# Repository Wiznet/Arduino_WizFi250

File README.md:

## Arduino_WizFi250

Arduino_WizFi250 library has been renamed [WizFi250_arduino_library](https://github.com/Wiznet/WizFi250_arduino_library)

This repo is obsolete and will be removed in the future.

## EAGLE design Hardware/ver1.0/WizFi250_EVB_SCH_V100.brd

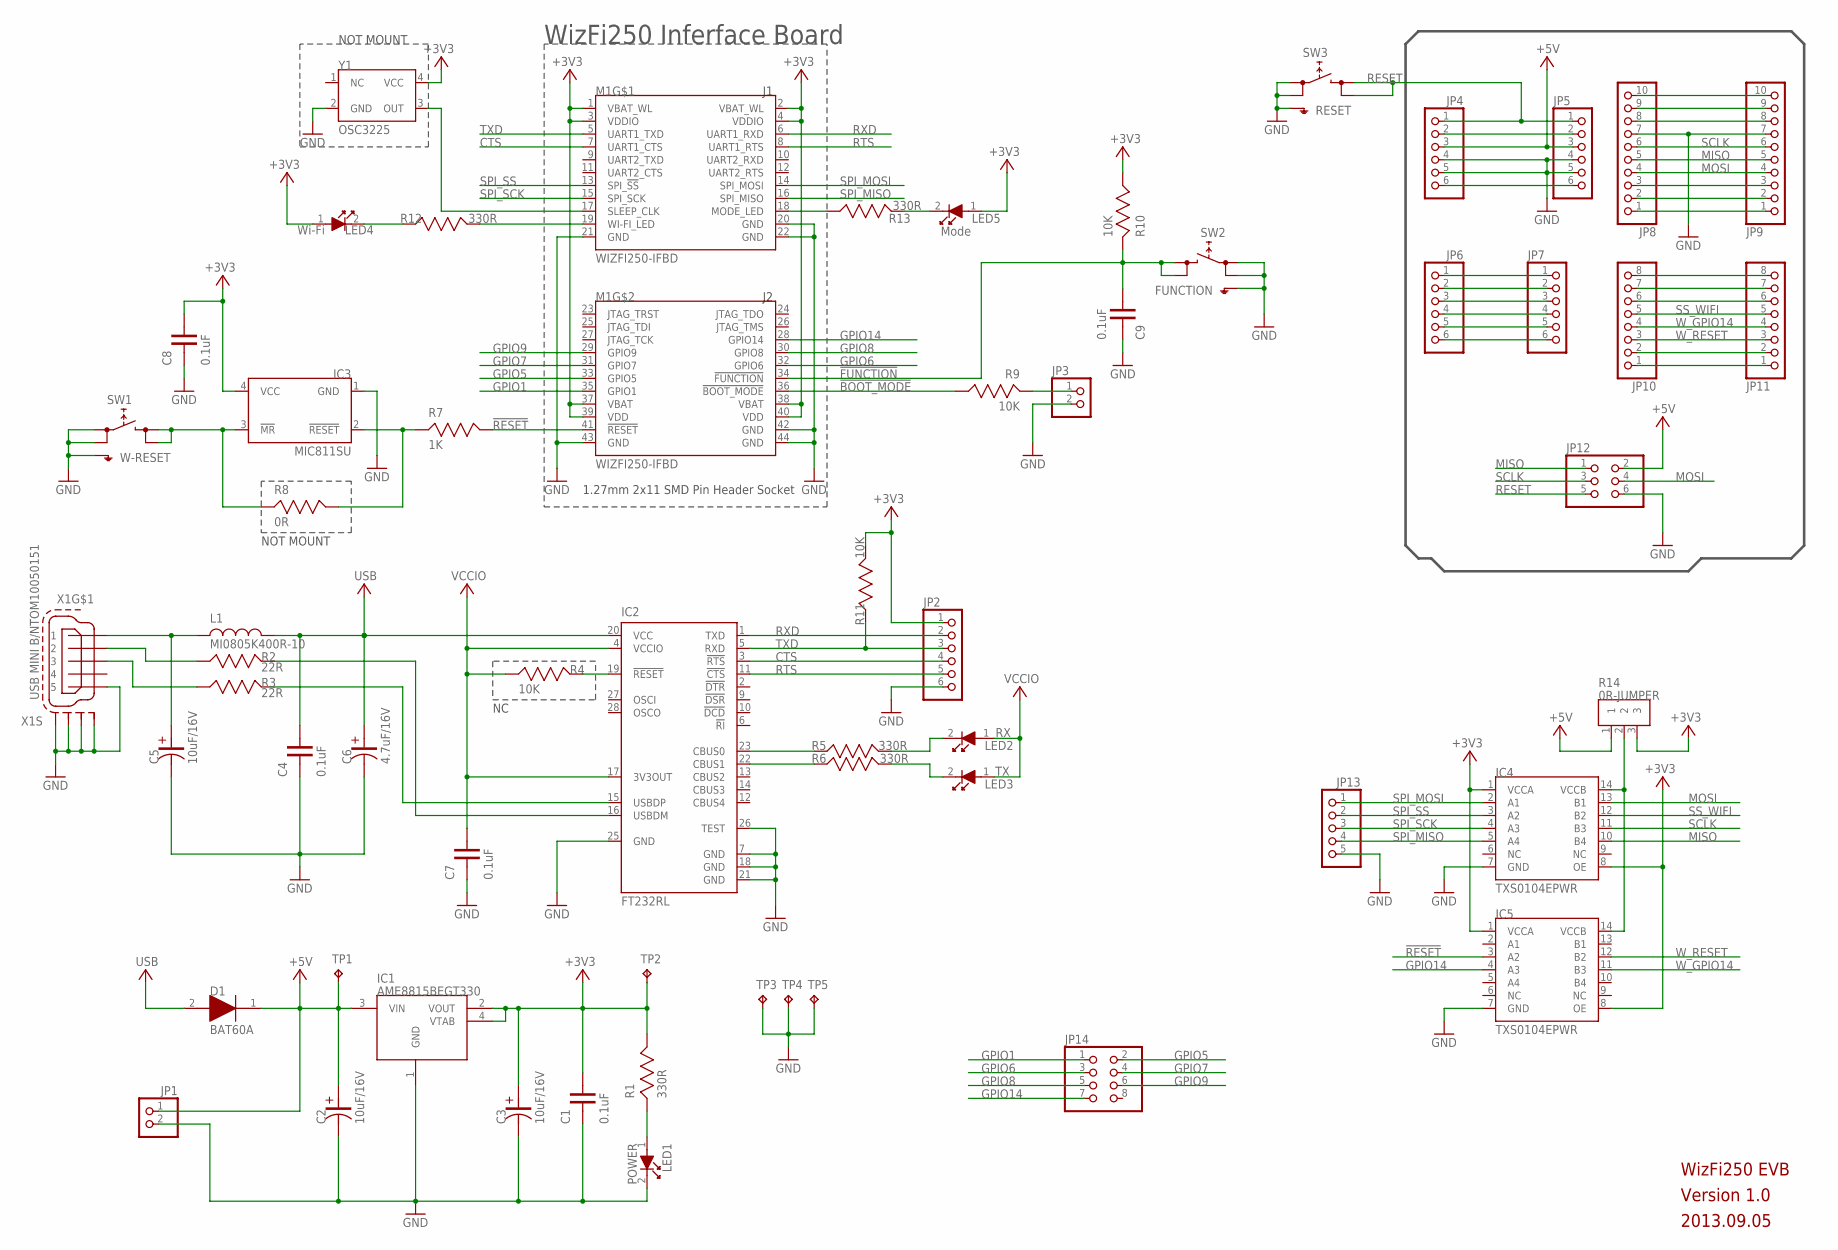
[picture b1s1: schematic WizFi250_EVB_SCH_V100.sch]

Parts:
C1, C4, C7, C8, C9: 0.1uF; C-1608
C2, C3, C5: 10uF/16V; C-3216(TANTAL)
C6: 4.7uF/16V; C-3216(TANTAL)
D1: BAT60A
IC1: AME8815BEGT330; SOT-223
IC2: FT232RL; SSOP28
IC3: MIC811SU
IC4, IC5: TXS0104EPWR
JP1, JP3: PINHD-1X2; 1X02
JP2, JP4, JP5, JP6, JP7: PINHD-1X6; 1X06
JP8, JP9: PINHD-1X10; 1X10
JP10, JP11: PINHD-1X8; 1X08
JP12: PINHD-2X3; 2X03
JP13: PINHD-1X5; 1X05
JP14: PINHD-2X4; 2X04
L1: MI0805K400R-10; L-2012
LED1: POWER; LED-1608
LED2: RX; LED-1608
LED3: TX; LED-1608
LED4: Wi-Fi; LED-1608
LED5: Mode; LED-1608
M1: WIZFI250-IFBD
R1, R5, R6, R12, R13: 330R; R-1608
R2, R3: 22R; R-1608
R4, R9, R10, R11: 10K; R-1608
R7: 1K; R-1608
R8: 0R; R-1608
R14: 0R-JUMPER; R-1608-JUMPER
SW1: W-RESET; SKHMPXE010
SW2: FUNCTION; SKHMPXE010
SW3: RESET; SKHMPXE010
TP1, TP2, TP3, TP4, TP5: TPB1,27; B1,27
X1: USB MINI B/NTOM10050151; 32005-201
Y1: OSC3225

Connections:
!RESET: IC5.3 (A2), M1.41 (!RESET), R7.2
+3V3: C1.2, C3.1, C8.2, IC1.2 (VOUT), IC1.4 (VTAB), IC3.4 (VCC), IC4.1 (VCCA), IC4.8 (OE), IC5.1 (VCCA), IC5.8 (OE), JP2.1, LED4.1, LED5.1, M1.1 (VBAT_WL), M1.2 (VBAT_WL), M1.3 (VDDIO), M1.4 (VDDIO), M1.37 (VBAT), M1.38 (VBAT), M1.39 (VDD), M1.40 (VDD), R1.2, R10.2, R11.2, R14.3, TP2.TP, Y1.4 (VCC)
+5V: C2.1, D1.1, IC1.3 (VIN), JP1.1, JP4.3, JP5.3, JP12.2, R14.1, TP1.TP
BOOT_MODE: M1.36 (!BOOT_MODE), R9.2
CTS: IC2.3 (!RTS), JP2.4, M1.7 (UART1_CTS)
FACTORY_RESET: C9.2, M1.34 (!FUNCTION), R10.1, SW2.3 (2.1), SW2.4 (2.2)
GND: C1.1, C2.2, C3.2, C4.1, C5.2, C6.2, C7.1, C8.1, C9.1, IC1.1 (GND), IC2.7 (GND), IC2.18 (GND), IC2.21 (GND), IC2.25 (GND), IC2.26 (TEST), IC3.1 (GND), IC4.7 (GND), IC5.7 (GND), JP1.2, JP2.6, JP3.2, JP4.4, JP4.5, JP5.4, JP5.5, JP8.7, JP9.7, JP12.6, JP13.5, LED1.2, M1.20 (GND), M1.21 (GND), M1.22 (GND), M1.42 (GND), M1.43 (GND), M1.44 (GND), SW1.1 (1.1), SW1.2 (1.2), SW1.5 (SH), SW2.1 (1.1), SW2.2 (1.2), SW2.5 (SH), SW3.1 (1.1), SW3.2 (1.2), SW3.5 (SH), TP3.TP, TP4.TP, TP5.TP, X1.5, X1.M1 (S1), X1.M2 (S2), X1.M3 (S3), X1.M4 (S4), Y1.2 (GND)
GPIO1: JP14.1, M1.35 (GPIO1)
GPIO5: JP14.2, M1.33 (GPIO5)
GPIO6: JP14.3, M1.32 (GPIO6)
GPIO7: JP14.4, M1.31 (GPIO7)
GPIO8: JP14.5, M1.30 (GPIO8)
GPIO9: JP14.6, M1.29 (GPIO9)
GPIO14: IC5.4 (A3), JP14.7, M1.28 (GPIO14)
MISO: IC4.10 (B4), JP8.5, JP9.5, JP12.1
MOSI: IC4.13 (B1), JP8.4, JP9.4, JP12.4
unnamed: IC4.14 (VCCB), IC5.14 (VCCB), R14.2
unnamed: R2.1, X1.2
unnamed: R3.1, X1.3
unnamed: LED1.1, R1.1
unnamed: JP3.1, R9.1
unnamed: IC2.16 (USBDM), R2.2
unnamed: IC2.15 (USBDP), R3.2
unnamed: IC2.19 (!RESET), R4.2
unnamed: IC3.2 (!RESET), R7.1, R8.2
unnamed: LED2.2, R5.2
unnamed: LED3.2, R6.2
unnamed: JP4.2, JP5.2
unnamed: JP4.6, JP5.6
unnamed: JP6.1, JP7.1
unnamed: JP6.2, JP7.2
unnamed: JP6.3, JP7.3
unnamed: JP6.4, JP7.4
unnamed: JP6.5, JP7.5
unnamed: JP6.6, JP7.6
unnamed: JP8.10, JP9.10
unnamed: JP8.9, JP9.9
unnamed: JP8.8, JP9.8
unnamed: JP8.3, JP9.3
unnamed: JP8.2, JP9.2
unnamed: JP8.1, JP9.1
unnamed: JP10.8, JP11.8
unnamed: JP10.7, JP11.7
unnamed: JP10.6, JP11.6
unnamed: JP10.2, JP11.2
unnamed: JP10.1, JP11.1
unnamed: M1.17 (SLEEP_CLK), Y1.3 (OUT)
unnamed: M1.19 (WI-FI_LED), R12.2
unnamed: LED4.2, R12.1
unnamed: M1.18 (MODE_LED), R13.1
unnamed: LED5.2, R13.2
RESET: JP4.1, JP5.1, JP12.5, SW3.3 (2.1), SW3.4 (2.2)
RTS: IC2.11 (!CTS), JP2.5, M1.8 (UART1_RTS)
RX-LED: IC2.23 (CBUS0), R5.1
RXD: IC2.1 (TXD), JP2.2, M1.6 (UART1_RXD)
SCLK: IC4.11 (B3), JP8.6, JP9.6, JP12.3
SPI_MISO: IC4.5 (A4), JP13.4, M1.16 (SPI_MISO)
SPI_MOSI: IC4.2 (A1), JP13.1, M1.14 (SPI_MOSI)
SPI_SCK: IC4.4 (A3), JP13.3, M1.15 (SPI_SCK)
SPI_SS: IC4.3 (A2), JP13.2, M1.13 (SPI_!SS)
SS_WIFI: IC4.12 (B2), JP10.5, JP11.5
TX-LED: IC2.22 (CBUS1), R6.1
TXD: IC2.5 (RXD), JP2.3, M1.5 (UART1_TXD), R11.1
USB: C4.2, C6.1, D1.2, IC2.20 (VCC), L1.2
VCC: C5.1, L1.1, X1.1
VCCIO: C7.2, IC2.4 (VCCIO), IC2.17 (3V3OUT), LED2.1, LED3.1, R4.1
WI-FI_RST: IC3.3 (!MR), R8.1, SW1.3 (2.1), SW1.4 (2.2)
W_GPIO14: IC5.11 (B3), JP10.4, JP11.4
W_RESET: IC5.12 (B2), JP10.3, JP11.3

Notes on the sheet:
NOT MOUNT
WizFi250 EVB
2013.09.05
Version 1.0
WizFi250 Inferface Board
1.27mm 2x11 SMD Pin Header Socket

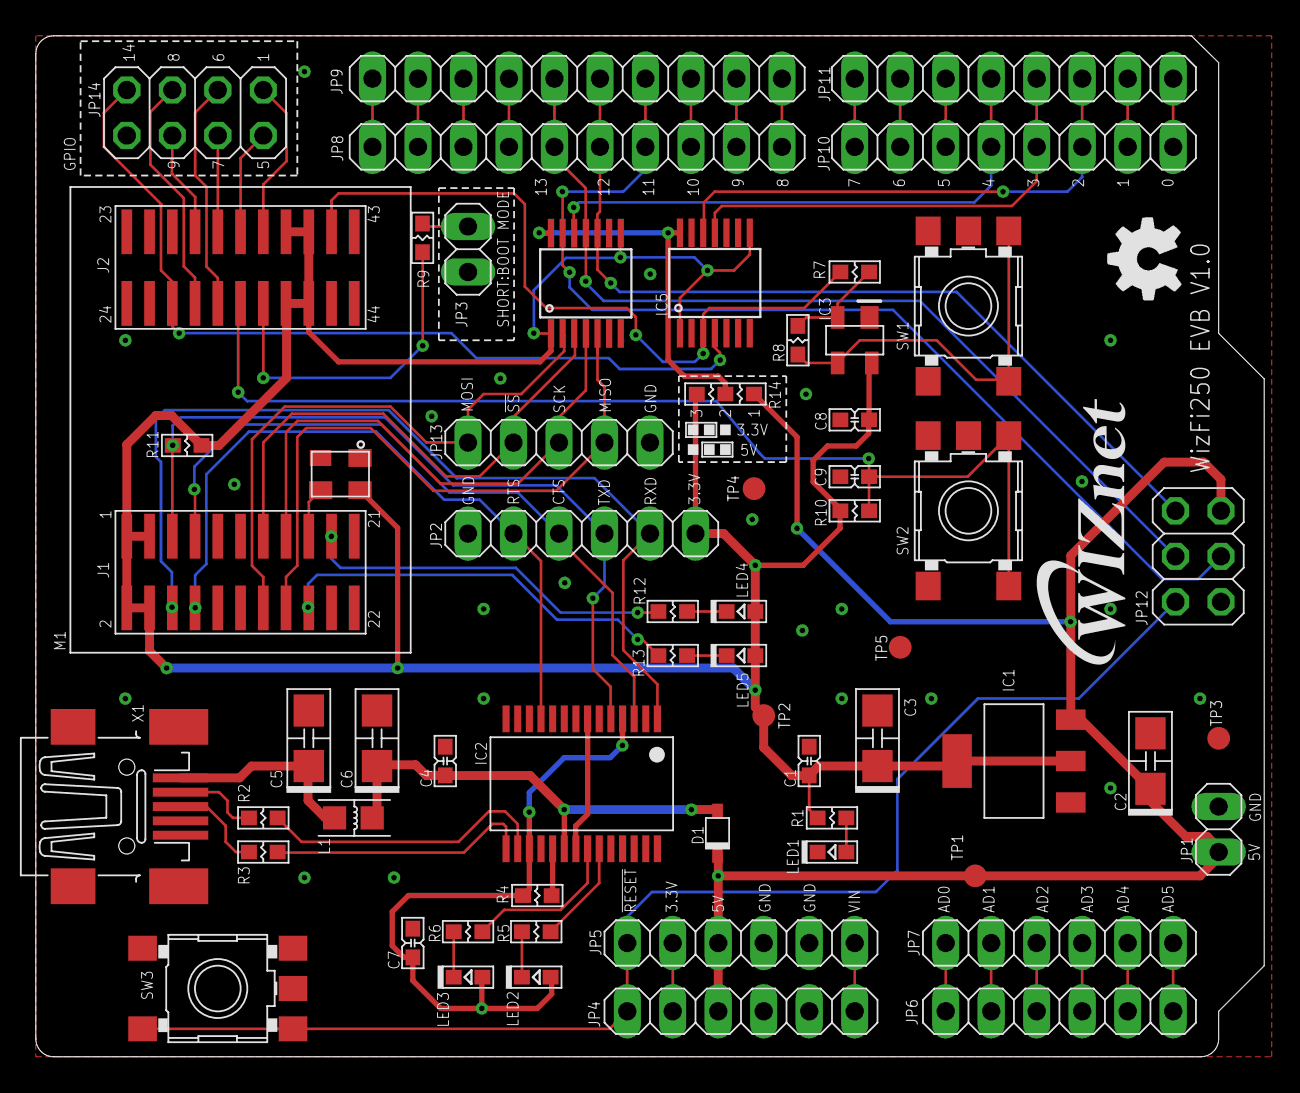
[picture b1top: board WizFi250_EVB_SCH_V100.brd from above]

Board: 2 copper layers, 68.6 x 57.0 mm, 62 parts (0 on the bottom side), 69 nets.

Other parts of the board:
U$1: OSHP-LOGO
U$2: WIZNET2-LOGO

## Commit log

2014-03-03 WizFi250 Arduino Library Release
    WizFi250 Arduino Library Release
2014-03-04 Added WizFi250 Hardware Data
2014-03-19 WizFi250 XivelyClient Example Bug Fix
    Fix the bug about XivelyClient Example
    Bug
    - WizFi250 hang up when occur [Disconnect] event
2014-03-20 Added WebServer Example
    Bug Fix
    - WizFi250's data was crashed when received more 256byte in TCP server.
2014-03-20 Added wleave command & modified recv function
    Added wleave command and modified WizFi250_Socket::recv() function
2014-03-20 Added RC Car Example
    Added RC Car Example.
    This example use TA8050P IC.
2014-03-25 Added WizFi250-EVB images
2014-03-25 Modified WizFi250-EVB_1 image
2014-03-25 Added WizFii250 Hardware schematic
2014-03-25 Change the file name of WizFi250-EVB_1
2014-04-21 Increse SPI speed per 1byte
    Increse SPI speed per 1byte
2014-09-18 modify in order to use avr-gcc up to 4.8.2
2014-09-18 Added Twitter example using WizFi250
2014-10-20 Solved the problem about compile error on 1.5.x version of Arduino Sketch
2018-07-10 Move library to root of repository
    A popular library installation technique is to download the library via GitHub's Clone or download > Download ZIP and then use the Arduino IDE's Sketch > Include Library > Add .ZIP Library on the dow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
    Specified folder/zip file does not contain a valid library
    This is the standard repository structure used in all official Arduino libraries:
    https://github.com/arduino-libraries
    This move is also required if you wanted to add your library to the Arduino Library Manager index, wh
